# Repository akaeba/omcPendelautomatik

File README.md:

# omcPendelautomatik
Circuit to drive a model train cyclic from one station to the other and back.

## Schematic

### Current Supervision

#### Current sensing and high-to-low conversion
The current sensor measures the voltage drop over an 0.5R shunt resistor. The high to low side voltage translation
is realized by [ZXCT1009](https://www.diodes.com/assets/Datasheets/ZXCT1009.pdf). According to the datasheet causes 
100mV voltage difference a output current of 1mA. Follows for V<sub>OUT</sub>:

with R<sub>SENSE</sub>=0.5 and R<sub>OUT</sub>=200:

#### Opamp signal conditioning
The current sensors output voltage is processed by an band-limited operational amplifier

##### Amplification
The following can be noted as a starting point:

All three equations inserted into each other:

For the amplification follows:

##### Band limit
A band limitation of the operational amplifier guarantees a good SNR and ADC resolution. An capacitor in parallel to R<sub>2</sub> limits the amplification.
The [Amplification](#Amplification) extended with an expression of the capacitive resistance follows:

After short calculation and solving the parallel operator:

Using the -3dB criteria

Follows

Solved for C

## Used Tools
* Eagle 7.7

## Libraries
* Eagle:
    * [omcEagleLib](https://github.com/gallioleo/omcEagleLib)

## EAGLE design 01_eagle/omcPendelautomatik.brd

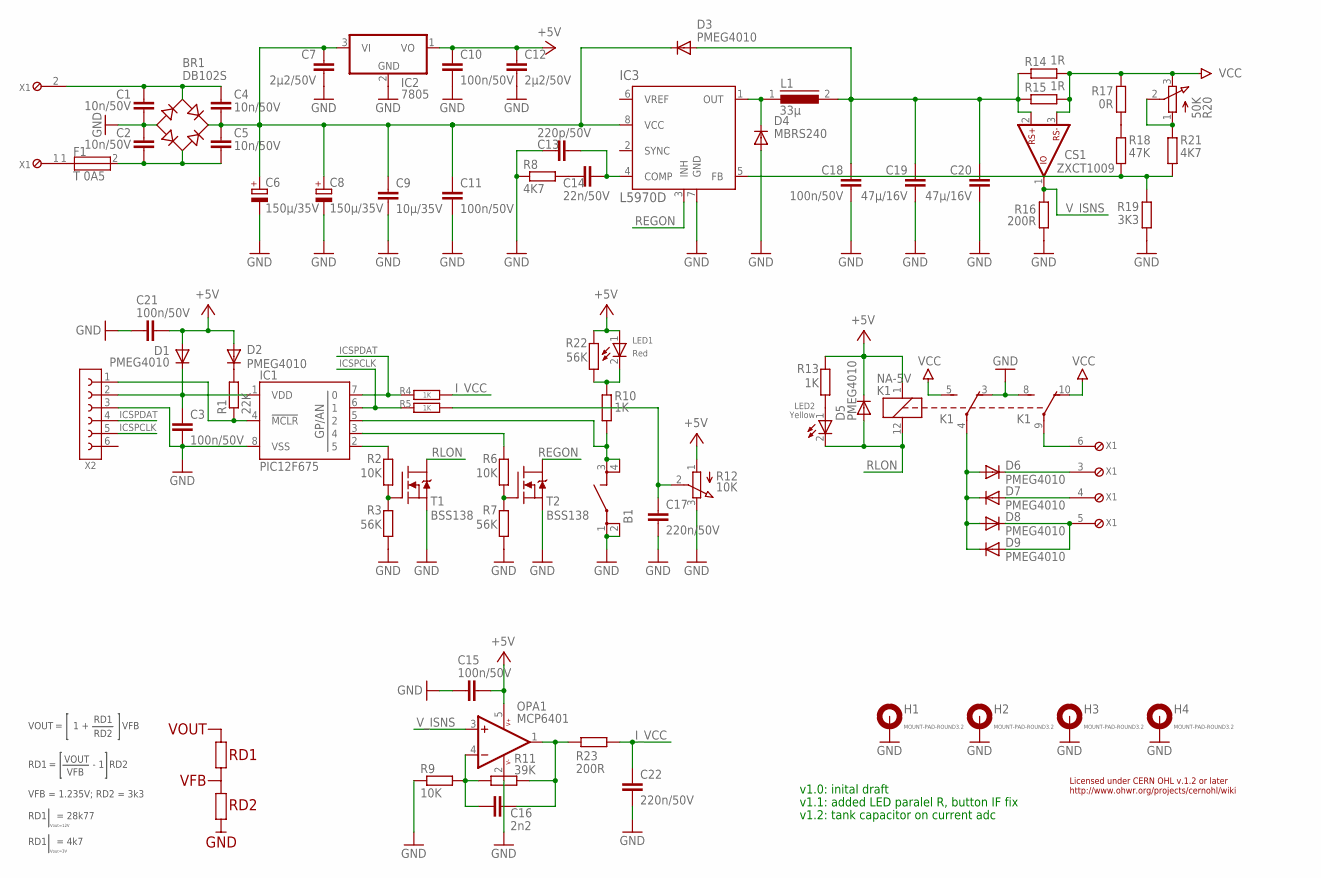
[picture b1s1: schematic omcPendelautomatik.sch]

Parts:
B1: JTP1138/4.3; SMD_X4_11X6
BR1: DB102S; DBS
C1, C2, C4, C5: 10n/50V; 1206
C3, C10, C11, C15, C18, C21: 100n/50V; 1206
C6, C8: 150µ/35V; PANF
C7, C12: 2µ2/50V; 1206
C9: 10µ/35V; 1210
C13: 220p/50V; 1206
C14: 22n/50V; 1206
C16: 2n2; 1206
C17, C22: 220n/50V; 1206
C19, C20: 47µ/16V; 1210
CS1: ZXCT1009; SOT23
D1, D2, D3, D5, D6, D7, D8, D9: PMEG4010; SOD323
D4: MBRS240; DO214AA
F1: T 0A5; OMT125
H1, H2, H3, H4: MOUNT-PAD-ROUND3.2; 3,2-PAD
IC1: PIC12F675; SOIC08
IC2: 7805; SOT89W
IC3: L5970D; SOIC08
K1: NA-5V; THT_5M08M_5M08M_2M54M
L1: 33µ; PISM
LED1: Red; LED3216
LED2: Yellow; LED3216
OPA1: MCP6401; SOT23-5
R1: 22K; 1206
R2, R6, R9: 10K; 1206
R3, R7, R22: 56K; 1206
R4, R5, R10, R13: 1K; 1206
R8, R21: 4K7; 1206
R11: 39K; 1206
R12: 10K; TTM44W
R14, R15: 1R; 1206
R16, R23: 200R; 1206
R17: 0R; 1206
R18: 47K; 1206
R19: 3K3; 1206
R20: 50K; TTM44W
T1, T2: BSS138; SOT23
X1: RT034 Typ 086; RT03406T086
X2: 2X3; BOXHD-06-2.54-S

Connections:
+5V: C10.1, C12.1, C15.2, C21.2, D1.A, D2.A, D5.C, IC2.1 (VO), K1.1 (2), LED1.1 (A), OPA1.5 (V+), R12.1 (A), R13.2, R22.2
GND: B1.1, B1.2, BR1.-, C1.2, C2.1, C3.2, C6.CN (-), C7.2, C8.CN (-), C9.2, C10.2, C11.2, C12.2, C13.1, C15.1, C17.2, C18.2, C19.2, C20.2, C21.1, C22.2, D4.A, H1.B3,2, H2.B3,2, H3.B3,2, H4.B3,2, IC1.8 (VSS), IC2.2 (GND), IC2.4 (GND), IC3.7 (GND), K1.3 (O), K1.8 (S), OPA1.2 (V-), R3.1, R7.1, R8.1, R9.1, R12.3 (E), R16.1, R19.1, T1.2 (S), T2.2 (S), X2.3
ICSPCLK: IC1.6 (1), R5.1, X2.5
ICSPDAT: IC1.7 (0), R4.1, X2.4
I_VCC: C22.1, R4.2, R23.1
unnamed: D4.C, IC3.1 (OUT), L1.1
unnamed: R20.1 (A), R20.2 (S), R21.2
unnamed: C13.2, C14.1, IC3.4 (COMP)
unnamed: C14.2, R8.2
unnamed: R2.1, R3.2, T1.1 (G)
unnamed: BR1.+, C4.2, C5.1, C6.CP (+), C7.1, C8.CP (+), C9.1, C11.1, D3.C, IC2.3 (VI), IC3.8 (VCC)
unnamed: C3.1, D1.C, IC1.1 (VDD), X2.2
unnamed: F1.1, X1.1
unnamed: IC3.5 (FB), R18.1, R19.2, R21.1
unnamed: IC1.4 (!MCLR!), R1.1, X2.1
unnamed: D2.C, R1.2
unnamed: IC1.2 (5), R2.2
unnamed: R6.1, R7.2, T2.1 (G)
unnamed: IC1.3 (4), R6.2
unnamed: LED2.1 (A), R13.1
unnamed: R17.1, R18.2
unnamed: BR1.AC1, C1.1, C4.1, X1.2
unnamed: D6.C, X1.3
unnamed: C17.1, R5.2, R12.2 (S)
unnamed: C16.1, OPA1.4 (-IN), R9.2, R11.1
unnamed: D7.A, X1.4
unnamed: D6.A, D7.C, D8.A, D9.C, K1.4
unnamed: BR1.AC2, C2.2, C5.2, F1.2
unnamed: K1.9, X1.6
unnamed: B1.3, B1.4, IC1.5 (2), R10.1
unnamed: D8.C, D9.A, X1.5
unnamed: LED1.2 (C), R10.2, R22.1
unnamed: C16.2, OPA1.1 (OUT), R11.2, R23.2
REGON: IC3.3 (INH), T2.3 (D)
RLON: D5.A, K1.12 (1), LED2.2 (C), T1.3 (D)
VCC: CS1.3 (-RS), K1.5 (S), K1.10 (O), R14.2, R15.2, R17.2, R20.3 (E)
VOUT: C18.1, C19.1, C20.1, CS1.2 (+RS), D3.A, L1.2, R14.1, R15.1
V_ISNS: CS1.1 (IOUT), OPA1.3 (+IN), R16.2

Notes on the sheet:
GND
VFB
VOUT
RD1
RD2
1 +
VFB = 1.235V; RD2 = 3k3
= 28k77
- 1
Vout=12V
= 4k7
Vout=3V
Licensed under CERN OHL v.1.2 or later http://www.ohwr.org/projects/cernohl/wiki
v1.1: added LED paralel R, button IF fix
v1.0: inital draft
v1.2: tank capacitor on current adc

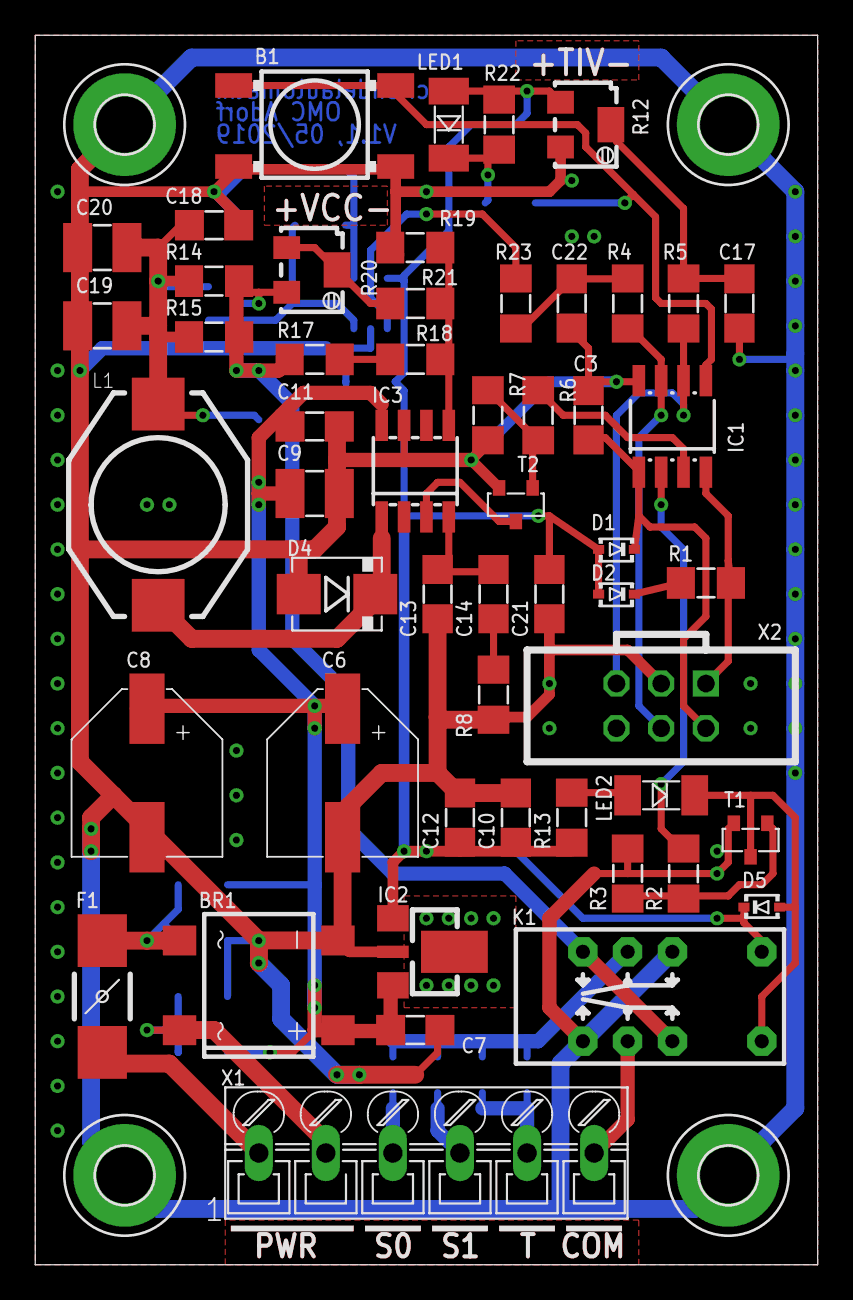
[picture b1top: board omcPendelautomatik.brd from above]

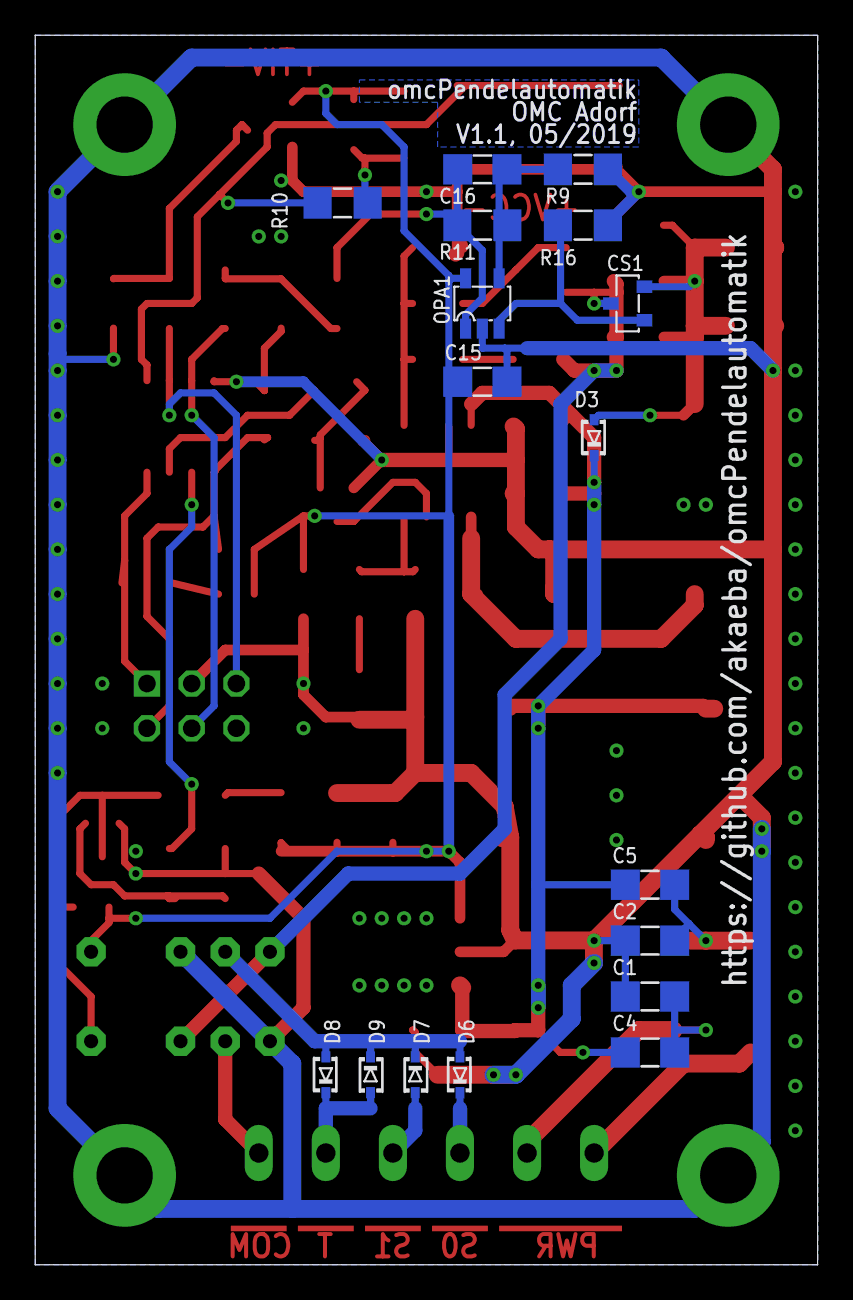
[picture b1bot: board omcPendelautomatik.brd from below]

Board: 2 copper layers, 44.5 x 69.8 mm, 74 parts (17 on the bottom side), 38 nets.

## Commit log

2019-02-16 README.md -> typing correction -> added link
2019-03-10 added TLC555 spice model -> SRC: https://www.mikrocontroller.net/topic/346361
2019-04-01 omcPendelautomatik.sch -> intermediate commit, due architecture change
2019-04-07 omcPendelautomatik.sch -> intermediate commit -> changed from '555' timing normal to 'uC'
2019-04-11 omcPendelautomatik.sch -> initial draft schematic finished
2019-04-19 omcPendelautomatik -> Placement and routing main parts done -> schematic changes for routing
2019-04-19 omcPendelautomatik.brd -> adjust silk print on top side
2019-04-21 omcPendelautomatik.brd -> adjust bottom side silk
2019-04-21 omcPendelautomatik -> symbol update -> added some vias to connect top/bottom ground plane
2019-04-22 omcPendelautomatik.brd -> added Polygon to avoid thermals at linear regulator
2019-04-22 omcPendelautomatik.brd -> adjust cap to avoid DRC error
2019-04-22 omcPendelautomatik_tapein.brd -> removed GND net and recalculated with ratsnest
2019-04-22 omcPendelautomatik -> added label with name and version
2019-04-22 omcPendelautomatik -> adjusted Ref Desg. for manufacturing
2019-04-23 omcPendelautomatik_Vadj -> added bom for adjustable voltage
2019-04-23 TLC555 -> removed cause not used
2019-04-23 update gitignore
2019-04-23 opamp -> added sim
2019-04-24 omcPendelautomatik_Vadj.txt -> corrected BOM entry
2019-04-24 omcPendelautomatik_Vadj-Reichelt.csv -> added order card for reichelt
2019-04-27 omcPendelautomatik -> added derived files
2019-05-01 gitignore adjust
2019-05-11 PCB pics
2019-05-26 bugfix uC button wiring
2019-05-26 gitignore for MikroC update
2019-06-15 omcPendelautomatik.sch -> added tank capacitor for current sense adc
2019-06-16 omcPendelautomatik -> initial draft w/o any test
2019-06-22 added tank caps for current sense adc, pcb done
2019-06-22 update derived file
2019-06-23 static divider by cmacro pow calc replaced
2019-06-29 some math
2019-06-29 math try
2019-06-29 include as pic
2019-06-29 test external render
2019-06-29 first formulas
2019-06-30 some formulas
2019-06-30 line breaks
2019-06-30 blank replace
2019-06-30 type error
2019-07-20 added formula für -3db frequency
2019-07-20 current transfer function
2019-07-20 minor change

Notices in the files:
parts and their libraries:
omcSwitch: Copyright & License
This library is free software: you can redistribute it and/or modify
it under the terms of the GNU General Public License as published by
the Free Software Foundation, either version 3 of the License, or
(at your option) any later version.
